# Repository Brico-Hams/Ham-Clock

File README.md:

# CYD Ham Dashboard – BricoHams edition

> **BricoHams edition** of the CYD Ham Dashboard, maintained by the BricoHams group with thanks to **EA5JEF, Diego** - **EA5KAO, Anatol**. It is based on the original project by [HenrysCat](https://github.com/HenrysCat/esp32-cyd-ham-dashboard) – many thanks for creating it. Documentation and the configuration manual are in [`docs/`](docs/README.md); full acknowledgements in [CREDITS.md](CREDITS.md).

A HamClock-inspired ham radio dashboard for the ESP32 Cheap Yellow Display, supporting both the 2.8" ESP32-2432S028R and the 4.0" 320x480 ST7796S variant from a single source tree.

**[Flash it in your browser with the Web Flasher](https://brico-hams.github.io/Ham-Clock/)**

## Reloj o Morse Tutor Bricohams

El suscriptor puede elegir entre **dos firmwares independientes**: este reloj,
o [Bricohams Morse Tutor](morse-tutor/README.md). Grabar uno sustituye al otro;
no se ha incorporado el tutor al bucle ni a las dependencias del reloj.
El [instalador del tutor](https://brico-hams.github.io/Ham-Clock/morse-tutor/)
se publica junto al existente mediante el workflow de GitHub Pages.

El tutor v2.1.1 es una nueva implementación Bricohams con menús por tarjetas,
perfil Freenove 3,2" FNK0114L/ST7789 y sala de mensajes para múltiples
tutores por ESP-NOW. Cada pantalla ofrece WiFi `Bricohams-CW-XXXXXX`
(clave `BricohamsCW`) para enviar desde el móvil sin Internet.
No es una red mesh ni RF de radioaficionado; consultar
[funcionamiento, límites y autoría](morse-tutor/README.md).
Incluye español, inglés, alemán, francés e italiano, con idioma de interfaz
y vocabulario independientes; entrenador eco, Koch configurable, práctica
adaptativa, ocho memorias, estadísticas y pausas Wordsworth.
En modo llave recta, el pulsador táctil **Llave CW** permite manipular y enviar
en Red CW sin llave externa, manteniendo pulsado para cada marca y soltando
para los espacios. En Iambic A/B conserva DIT/DAH virtuales.
El perfil Freenove es del tutor: no se añade automáticamente al reloj.

El subproyecto incluye una interfaz cableada de llave/audio con Gerber y cajas
paramétricas imprimibles para reloj con batería y tutor con palas mecánicas.
Son **prototipos pendientes de validación física**, no hardware certificado.
Consulta [alimentación, conexiones y fabricación](morse-tutor/hardware/README.md)
y [las medidas de las cajas](morse-tutor/mechanical/README.md) antes de fabricar.
El [tutorial ilustrado y manual detallado](https://brico-hams.github.io/Ham-Clock/morse-tutor/docs/manual.html)
incluye todos los ajustes y capturas web con datos simulados, además de
ilustraciones TFT claramente identificadas.
El [catálogo de cajas](https://brico-hams.github.io/Ham-Clock/morse-tutor/docs/cajas.html)
ofrece 36 bases/tapas de nueve variantes, incluidas Sunton 3,2" N/R/C y otras
familias documentadas. Las nuevas cajas no añaden perfiles de firmware ni
certifican el ajuste de las envolventes provisionales.

Los perfiles del reloj y del tutor fijan `espressif32@6.13.0` (Arduino-ESP32
2.0.17). El reloj utiliza la API LEDC 2.x; una plataforma sin versión puede
seleccionar Arduino 3.x y romper la compilación del instalador. No se ha cambiado
la lógica del reloj para corregirlo.

It provides a touch-controlled landscape dashboard — 320x240 on the 2.8" board, 480x320 on the 4.0" — with UTC/local time, HamQSL propagation data, a greyline map, DX spots, Wi-Fi setup, and a local web settings page. The 4.0" board uses the extra room rather than simply scaling up: larger text on the data pages, and twelve DX/POTA spots in place of eight.

## Features

- ESP32-2432S028R / CYD ILI9341 display support
- XPT2046 touch navigation
- Thirteen dashboard pages, plus an optional ISS tracker and an optional Music page (MP3 from microSD):
  - Clock
  - HF Propagation from HamQSL
  - VHF Conditions from HamQSL
  - Greyline map with QTH marker, sun marker, terminator, sunrise/sunset, and day/night status
  - PSKReporter reception reports for your callsign, plotted on the same world map
  - ISS Tracker: current position and ground track on the same world map, plus upcoming passes (optional; hidden until a free N2YO API key is set)
  - DX spots from JSON and/or a persistent Telnet DX Cluster connection
  - POTA activator spots, with an optional distance filter from your locator
  - OpenWebRX status and live chat
  - DMR Last Heard from compatible hotspots
  - World Clock with UTC and ten city clocks
  - Nearest APRS weather station and recent weather data
  - Nearby APRS nodes and stations, ordered by distance from your locator
  - Live APRS map: range-ring view centred on your QTH with every station heard in the last hour (tap to zoom)
- Captive portal Wi-Fi setup with up to five remembered networks; it automatically joins a saved network in range and switches off the hotspot a few seconds after connection (it can be switched back on from the web settings page if you need it again)
- Local web settings page on the device IP
- Hold the BOOT button on the back of the board for 5 seconds to factory reset all settings
- Optional mDNS address: `http://cyd-ham.local/`
- NTP time sync
- Configurable callsign, locator, timezone, data URLs, refresh intervals, and brightness
- Optional automatic page change, cycling only the pages you tick at your chosen interval
- Optional night dimming, fading the backlight between a day and a night level across sunrise and sunset
- Settings stored in ESP32 non-volatile preferences
- No LVGL, SD card, or external filesystem required

## Hardware

Three tested targets, plus one untested Freenove target, all ESP32-WROOM based with an XPT2046 resistive touch controller:

| Board | Panel | PlatformIO env | Setup header |
| --- | --- | --- | --- |
| ESP32-2432S028R 2.8" | ILI9341 320x240 | `esp32-2432s028r` | `include/User_Setup.h` |
| ESP32-2432S028R 2.8" | ST7789 320x240 | `esp32-2432s028r-st7789` | `include/User_Setup_ST7789.h` |
| CYD 4.0" | ST7796S 480x320 | `esp32-4in-st7796` | `include/User_Setup_ST7796.h` |
| Freenove ESP32 Display 3.2" (FNK0103L) | ST7789 320x240 | `freenove-32-st7789` | `include/User_Setup_Freenove32.h` |

**Freenove FNK0103 (3.2" ST7789):** same 320x240 layouts as the 2.8" CYD. The
touch controller shares the display bus and has no interrupt line, so touches are
detected from the pressure reading; the backlight is on GPIO27 and the speaker
amplifier is enabled by GPIO4. The pin map comes from the BricoHams Morse Tutor's
Freenove profile; the dashboard has not yet been tested on this board. If colours
or orientation are wrong, use the Display settings (swap red/blue, flip, mirror).

TFT_eSPI binds its panel driver at compile time, so the board is chosen by the
environment you build, not at runtime. Each environment force-includes its own
setup header, which carries the pins, the panel size, and the `DISPLAY_W` /
`DISPLAY_H` values the page layouts are derived from. Everything board-specific
lives in those headers rather than in the source.

### 2.8" wiring (ESP32-2432S028R)

| Signal | GPIO |
| --- | ---: |
| TFT MISO | 12 |
| TFT MOSI | 13 |
| TFT SCLK | 14 |
| TFT CS | 15 |
| TFT DC | 2 |
| TFT RST | -1 |
| TFT backlight | 21 |
| Touch SCLK | 25 |
| Touch MOSI | 32 |
| Touch MISO | 39 |
| Touch CS | 33 |
| Touch IRQ | 36 |

### 4.0" wiring (ST7796S)

The display pins match the 2.8" board. The two differences are the backlight,
which moves to GPIO 27, and the touch controller, which shares the display's
SPI bus instead of having its own. `dashboard_display.cpp` detects the shared
bus by comparing the touch pins against the TFT pins, and uses
`TFT_eSPI::getSPIinstance()` rather than starting a second bus.

| Signal | GPIO |
| --- | ---: |
| TFT MISO | 12 |
| TFT MOSI | 13 |
| TFT SCLK | 14 |
| TFT CS | 15 |
| TFT DC | 2 |
| TFT RST | -1 |
| TFT backlight | **27** |
| Touch SCLK | **14** (shared) |
| Touch MOSI | **13** (shared) |
| Touch MISO | **12** (shared) |
| Touch CS | 33 |
| Touch IRQ | 36 |

This board also sets `USE_HSPI_PORT`. GPIO 12/13/14/15 are the ESP32's native
HSPI pins, so the peripheral can drive them through IOMUX and run the panel at
80MHz; without it TFT_eSPI defaults to VSPI, routes the signals through the GPIO
matrix, and the display breaks up into coloured noise above about 27MHz.

Some CYD variants use different pins. If the display is blank, white, mirrored, or touch is wrong, check your board revision and adjust the setup header for your environment and the touch constants in `src/dashboard_display.cpp`.

### Setup hotspot and factory reset

On first boot (or whenever no Wi-Fi is configured), the device broadcasts a `CYD-HamClock-Setup` access point (password `hamclock`) so you can join it and open the captive portal to enter your Wi-Fi details. Once the device confirms it has joined your network, the hotspot automatically switches off. To bring it back later — for example to reach the settings page again without your router — check "Keep the setup hotspot switched on" in the Station section of the web settings page.

The board's BOOT button (GPIO0, on the back next to the USB connector) doubles as a factory reset button: hold it down for 5 seconds while the dashboard is running to wipe all saved settings (Wi-Fi credentials, callsign, locator, timezone, data sources, brightness) and reboot to defaults. The screen shows a countdown while the button is held; release early to cancel.

## Flashing A Release Binary

If a `.bin` firmware file is attached to a GitHub release, you can flash it without building from source. The panel driver is compiled in, so each board has its own binary — check the release notes and pick the one matching your display, as the wrong binary will boot but show nothing usable.

Install `esptool`:

```sh
python -m pip install esptool
```

Put the board into normal USB flashing mode, then flash the release binary. Replace `COM5` and the filename as needed:

```sh
esptool.py --chip esp32 --port COM5 --baud 460800 write_flash -z 0x10000 firmware.bin
```

If the release includes bootloader and partition binaries, use the release instructions for those exact offsets. For PlatformIO-built firmware, the application binary normally goes at `0x10000`.

After flashing, the board will start its setup access point if Wi-Fi is not configured.

### Publishing the Web Flasher

The browser flasher lives in [`webflasher/`](webflasher/index.html) and uses [ESP Web Tools](https://esphome.github.io/esp-web-tools/). `tools/build_webflasher.py --build` builds every board variant and stages the bootloader, partition table, `boot_app0` and application image with a `manifest.json` per board in `webflasher/firmware/`. The script refuses to run while `include/app_config.local.h` exists, because that file would compile your Wi-Fi password and API keys into the public images.

The `Web Flasher` GitHub Actions workflow runs the script and deploys `webflasher/` to GitHub Pages whenever a `v*` tag is pushed, or when it is started by hand. Enable Pages with the source set to **GitHub Actions** in the repository settings first.

## Building From Source

Install:

- VS Code
- PlatformIO extension
- USB serial driver for your ESP32 board if required

Clone the repository and open it in VS Code.

Copy the example config to a git-ignored local override file:

```sh
copy include\app_config.example.h include\app_config.local.h
```

On macOS/Linux:

```sh
cp include/app_config.example.h include/app_config.local.h
```

Set per-device Wi-Fi, locator, callsign, timezone, service URLs, and API keys in `include/app_config.local.h`. That file is ignored by Git. Alternatively, configure Wi-Fi and dashboard settings from the captive portal or local web page.

Build. With no environment given this builds **all three**, which is a useful
check that a change suits every board but is not what you want before a flash:

```sh
pio run
```

Build and upload one board. Always pass `-e`, or the upload runs for each
environment in turn and leaves the last one on the board:

```sh
pio run -e esp32-2432s028r      -t upload   # 2.8" ILI9341
pio run -e esp32-2432s028r-st7789 -t upload # 2.8" ST7789
pio run -e esp32-4in-st7796     -t upload   # 4.0" ST7796S
```

Open Serial Monitor:

```sh
pio device monitor
```

## First Boot And Wi-Fi Setup

The ESP32 starts a setup access point while also trying to connect to saved Wi-Fi credentials.

- AP name: `CYD-HamClock-Setup`
- AP password: `hamclock`
- Portal address: `http://192.168.4.1`

Join the setup AP from a phone or computer. The captive portal may open automatically. If it does not, browse to:

```text
http://192.168.4.1
```

The setup page lets you configure:

- Callsign
- Up to five Wi-Fi SSID/password pairs; existing saved networks remain available when adding another one
- Timezone preset, label, and POSIX timezone rule
- Maidenhead locator
- 12-hour or 24-hour local clock on the clock page
- Propagation data source
- DX source mode, JSON URL, and Telnet host/port
- Refresh intervals
- Automatic page change, with the dwell in seconds and which pages take part
- Backlight brightness, and optional night dimming with its own level and fade length
- Display colour swap/invert and orientation (90-degree rotate, 180-degree flip, mirror) for differently wired CYD panels
- Touch page navigation direction swap for differently wired touch controller variants

Settings are saved to ESP32 Preferences and persist after reboot.
Saved Wi-Fi passwords are never displayed. Leave a password field blank to keep it, use its checkbox to clear it for an open network, or clear its SSID to remove that remembered network.

## Local Web Settings

When connected to Wi-Fi, the same settings page is available on your LAN:

```text
http://device-ip/
```

The clock page shows the current IP address. If mDNS starts successfully, this address may also work:

```text
http://cyd-ham.local/
```

Available routes:

- `GET /` - settings and status page
- `POST /save` - save settings
- `GET /status` - JSON status
- `POST /reboot` - restart the ESP32

This web UI is intended for a trusted local network. It does not include authentication.

## Touch Controls

- Tap left side: next page
- Tap right side: previous page
- Tap centre on HF Propagation or VHF Conditions page: manual propagation refresh
- Tap centre on DX Spots page: manual DX refresh
- Tap centre on PSKReporter page: queue a manual PSKReporter refresh (it runs once the five minute minimum interval has elapsed)
- Tap centre on ISS Tracker page: manual position and pass refresh
- Tap centre on POTA Spots page: manual POTA refresh
- Music page: the button row above the footer plays/pauses, skips and sets the volume (see below)

The footer shows Wi-Fi status, NTP status, and current page number. On every page except the Clock it also shows the current UTC time (the Clock page omits this since it already shows a full UTC readout above).

The Automatic Page Change section of the web settings page can cycle the dashboard on its own. Set how many seconds each page is shown (3 to 600) and tick which pages take part; unticked pages are skipped by the cycle but are still reachable by tapping. The ISS Tracker page is the one exception: while it is switched off, or has no API key set, it is left out of both the cycle and the left/right tap navigation entirely, rather than just being unticked. Any tap restarts the countdown, so a page being read is not pulled away mid-look.

If a DX or POTA row is part way through scrolling in when the countdown expires, the change waits for the list to settle rather than cutting the slide off, then turns the page immediately. A three second grace cap keeps a busy Telnet feed from parking the rotation on one page.

## Night Dimming

The Display section of the web settings page can fade the backlight down after dark. Set a night brightness percent and a fade length in minutes, and the backlight moves between the daytime brightness and the night level across a window centred on each crossing: a 40 minute fade starts 20 minutes before sunset and finishes 20 minutes after, then reverses at sunrise.

Sunrise and sunset come from your Maidenhead locator, the same figures the Greyline page shows, so set the locator correctly first. The settings page prints the current sun state and today's sunrise and sunset next to the controls. Before NTP has synced, or with dimming switched off, the daytime brightness is used.

The `/status` endpoint reports `backlight` (the level actually being driven, which sits between the two settings during a fade) and `sun`, so the fade can be watched at dusk without staring at the panel.

## Dashboard Pages

### Clock

Shows:

- Large UTC time
- Configured local time, in 24-hour or 12-hour with AM/PM (web settings page, Time and Location)
- Date
- Callsign and Maidenhead locator
- Device IP
- Uptime
- Wi-Fi/NTP/footer status

### HF Propagation

Fetches HamQSL data directly by default:

```text
https://www.hamqsl.com/solarxml.php
```

Displays:

- SFI
- A index
- K index
- X-Ray
- Sunspots
- Solar wind speed (SW) and magnetic-field Bz
- Geomag
- Noise
- Aurora
- HamQSL band condition groups for day/night
- Last update time and status

An optional JSON proxy URL can be configured from the web page.

### VHF Conditions

Same layout and data source as HF Propagation, sharing the same refresh cycle and JSON proxy setting.

Displays:

- SFI, A index, K index, X-Ray, Sunspots, Solar wind/Bz, Geomag, Noise, Aurora (identical top rows to HF Propagation)
- HamQSL VHF phenomena: VHF Aurora (with auroral latitude, when supplied), and E-Skip conditions for 6m Europe, 4m Europe, 2m Europe, and 2m North America
- Last update time and status

### Greyline

Calculates locally using the configured Maidenhead locator and NTP time.

Displays:

- Bitmap-style world map
- QTH marker
- Sun/subsolar marker
- Day/night terminator
- Night-side shading
- Sunrise, sunset, UTC time
- Location/daylight/greyline status

Changing the Maidenhead locator refreshes the Greyline calculations and map immediately; no reboot is required.

### PSKReporter

Plots recent PSKReporter reception reports for the configured callsign on the same world map the Greyline page uses.

Displays:

- One marker per four-character grid square, coloured by band
- QTH marker
- Grid and report counts for the selected time window
- Furthest report (callsign, locator, great-circle distance)
- A legend naming only the bands currently present, each in its marker colour

Settings:

- `Direction`: `Who is hearing me` (default) queries `senderCallsign`; `Who I am hearing` queries `receiverCallsign`
- `Report window minutes`: how far back to ask for, 5 to 360, default 60
- `PSKReporter refresh minutes`: 5 to 120, default 5
- `Contact email`: optional, sent as `appcontact`

The page needs a callsign to work. With the callsign field blank it shows the map and a prompt to set one, and makes no requests.

### APRS Weather and Nearby Stations

Both pages use a receive-only TCP connection to APRS-IS with the standard
`pass -1` login and a server-side radius filter centered on the configured
Maidenhead locator. The Station callsign is used to identify the client; the
dashboard never transmits or gates packets. The connection starts the first
time an APRS page is opened and remains active in the background while Wi-Fi is
connected, so weather beacons can arrive between carousel visits.

`APRS nearby radius` in web settings accepts 10 to 300 km (default 100 km).
The weather page selects the closest weather-bearing position packet and shows
available APRS weather fields in metric units. The nearby page lists up to six
stations, sorted by distance; comments containing common digipeater, LoRa, DMR,
or repeater identifiers are labelled as nodes. Data availability depends on
stations transmitting within range and APRS-IS connectivity.

An optional personal APRS.fi API key can enrich the nearest station's weather
data. The key is requested only while the weather page is active, no more than
once every 15 minutes, and is never bundled as a shared key. APRS.fi is credited
on the weather page and in the settings page, with a link to its service. Before
distributing builds with this integration, each user must configure their own
key and the publisher should contact APRS.fi as required by its API terms.

PSKReporter asks that reception data is retrieved no more often than once every five minutes. The firmware enforces that as a hard floor: the refresh setting will not go below five minutes, and a manual refresh from the touch screen or from saving settings is queued rather than run immediately if the last request was more recent than that. A `503` response, which is how PSKReporter turns away a client querying too often, is shown as `Rate limited` on the status line.

Reports are read straight off the socket one XML element at a time and never buffered whole, so an active callsign returning hundreds of reports costs no more RAM than a quiet one. Up to 48 grid squares are plotted; the furthest-report line considers every report returned, not just the plotted ones.

### ISS Tracker

Plots the current position of the ISS on the same world map the Greyline and PSKReporter pages use, draws its ground track either side of now, and lists upcoming passes over your configured locator. Position and track are computed on-device with [SGP4](https://github.com/Hopperpop/Sgp4-Library) orbital propagation from a TLE fetched periodically from [Celestrak](https://celestrak.org/), so they update often (every 20 seconds) and cost no network requests beyond the daily TLE refresh. Passes still come from the free [N2YO](https://www.n2yo.com/api/) REST API's `radiopasses` endpoint, since correctly searching a topocentric elevation curve for AOS/max-elevation/LOS is exactly the kind of thing better left to a service that already does it, and N2YO's free-tier limit for that endpoint (100 requests/hour) comfortably covers an hourly refresh. `radiopasses` rather than `visualpasses` deliberately: hams care about any pass above the elevation threshold for an RF contact (APRS, voice repeater, SSTV), not just the rarer passes where the ISS is sunlit against a dark sky.

Displays:

- ISS marker on the world map, alongside the QTH marker
- Ground track for roughly the 45 minutes either side of now (about half the ISS's ~93 minute orbit), as a thin line; a segment is skipped rather than drawn wherever the track crosses the antimeridian
- Current latitude/longitude and altitude, in both km and miles
- Current azimuth and elevation - i.e. where to actually point - alongside the next pass line
- Next pass: rise time (UTC), maximum elevation, duration
- Every pass after that which still fits the row: four on the 2.8" boards, up to five on the 4.0" (matching the DX/POTA pages' precedent of the taller board showing more rows rather than just bigger text)

Settings:

- `Show ISS tracker page`: off by default
- `N2YO API key`: free, from [n2yo.com/api](https://www.n2yo.com/api/) — used only for the pass list; position and track work without it once the TLE has been fetched, but the page stays hidden until a key is set regardless

This is the one dashboard page that is not always present. With the checkbox off, or the key blank, it is left out of both the automatic page cycle and manual left/right navigation entirely — the dashboard behaves exactly as it did before this page existed. Turning it on and setting a key adds it immediately, no reboot required.

Passes are only searched up to two days out and down to a 10 degree minimum elevation, which is the same trade every ham pass predictor makes between screen space and usefulness.

### DX Spots

Supports three source modes:

- `Auto` (default): backfill the list from JSON, then keep a Telnet connection open and add live spots on top of it
- `JSON`: use only the configured JSON feed
- `Telnet`: maintain a connection to the configured DX Cluster

In `Auto`, JSON fills the list in one request so the page is useful within seconds of boot, and Telnet then delivers spots live, one at a time. Once Telnet is delivering it keeps the list and JSON is left alone; JSON refreshes again only while Telnet has yet to deliver, or if the connection drops or falls silent for 10 minutes. A Telnet connection that cannot reach the cluster does not disturb the JSON list on screen.

The default JSON endpoint is:

```text
https://web.cluster.iz3mez.it/spots.json
```

Displays recent spots with:

- Frequency
- Callsign
- Mode, inferred where possible
- UTC time
- Last update time and status

The list holds eight spots on the 2.8" boards and twelve on the 4.0". A new
Telnet spot pushes the rows down one pitch, animated by rendering the incoming
row and the rows already on screen into a sprite and pushing a shifted window of
it each frame.

The default Telnet cluster is `dxspots.com:7300`. The configured station callsign is used for login, or `NOCALL` if no callsign is set. Both sources are configurable from the web settings page.

The device keeps the last good spot list when a refresh or connection fails. The DX page shows whether the active data came from JSON, Telnet, or the last good result.

## Configuration Files

### `include/app_config.local.h`

Optional per-device defaults. Copy from `include/app_config.example.h`; this
file is ignored by Git so credentials and private service URLs stay local.

Useful defaults:

```cpp
#define WIFI_SSID ""
#define WIFI_PASSWORD ""
#define MAIDENHEAD_LOCATOR "AA00"
#define APP_SETTINGS_NAMESPACE "cyd-hamclock"
#define TIMEZONE_DEFAULT "UTC0"
#define TIMEZONE_LABEL_DEFAULT "UTC"
#define CALLSIGN_DEFAULT ""
#define OPENWEBRX_URL_DEFAULT ""
#define DMR_HOTSPOT_URL_DEFAULT ""
#define N2YO_API_KEY_DEFAULT ""
#define PROPAGATION_JSON_URL ""
#define DX_SPOTS_URL ""
```

`include/app_config.h` supplies safe generic fallbacks. Values saved through the captive portal or web settings page override most defaults at runtime.
When no DX URL has been saved, `DX_SPOTS_URL` is used if configured; otherwise the public IZ3MEZ endpoint is used.

### `include/User_Setup*.h`

TFT_eSPI display configuration. There is one per board, and PlatformIO
force-includes the right one from that environment's `build_flags`:

```ini
build_flags =
  -D USER_SETUP_LOADED=1
  -include include/User_Setup.h          ; or _ST7789.h / _ST7796.h
```

Because the header is force-included into every translation unit, the
`DISPLAY_W` and `DISPLAY_H` it defines are visible project-wide. The page
layouts derive their geometry from those two values, and `src/dx_spots.h` and
`src/pota_spots.h` use `DISPLAY_H` to size the spot arrays — eight rows on the
2.8" boards, twelve on the 4.0".

## Timezones

The web settings page includes common timezone presets. The firmware uses POSIX timezone strings.

UK default:

```text
GMT0BST-1,M3.5.0/1,M10.5.0/2
```

UTC:

```text
UTC0
```

If your country is not listed, choose `Custom POSIX TZ` and enter a POSIX rule manually.

### POTA Spots

Live Parks on the Air activator spots from `https://api.pota.app/spot/activator`.

Displays `Freq | Call | Mode | Park`, newest spot first. The park reference takes the column DX Spots uses for time, since the reference is what you need in order to log the contact.

New spots scroll in one at a time using the same animation as the DX Spots page. Both pages share one set of row state and one scroll sprite, since only one of them can be on screen at a time; they differ only in the header of the last column.

Settings:

- `Max distance km`: great-circle distance from your Maidenhead locator. `0` (the default) shows everything.
- `POTA refresh minutes`: 1 to 120, default 5.
- `Hide RBN spots`: RBN entries are posted automatically by skimmers rather than by a person.

The status line reports how many spots were shown out of how many the feed returned, plus how many the filters rejected, so a short list explains itself.

Notes and limits:

- POTA publishes no formal rate limit. Existing client libraries settle on one request a minute, so that is enforced as a hard floor regardless of the refresh setting.
- The feed returns roughly a hundred spots in no guaranteed order. They are read one JSON object at a time and never buffered as a whole array, and the newest eight that pass the filters are kept.
- Repeat spots of the same activator at the same park are collapsed into one row, so a heavily spotted station cannot crowd out everyone else.
- Spots without coordinates are always shown, even when a distance limit is set, since there is no way to tell whether they are near or far.
- SOTA is deliberately not included. The `api2.sota.org.uk` endpoint currently returns a notice that it is deprecated and due for removal, so it is left until the replacement API is settled.

## Data Refresh

Default refresh intervals:

- HF Propagation: 15 minutes
- DX JSON: 5 minutes
- DX Telnet: persistent connection with reconnect attempts limited to once every 30 seconds
- PSKReporter: 5 minutes, which is also the lowest interval the service permits
- POTA: 5 minutes, with a one minute hard floor
- ISS Tracker: position/track every 20 seconds (local SGP4 computation, no network cost), TLE once a day, passes every hour (all fixed, not user-configurable)
- Greyline calculations: once per minute
- Clock: once per second

Propagation, DX, and PSKReporter refresh intervals can be changed in the web settings page.

## Project Structure

```text
include/
  User_Setup.h              TFT_eSPI pin setup, 2.8" ILI9341
  User_Setup_ST7789.h       TFT_eSPI pin setup, 2.8" ST7789
  User_Setup_ST7796.h       TFT_eSPI pin setup, 4.0" ST7796S
  app_config.example.h      Example local config
  greyline_map.h            Embedded Greyline map bitmap, 300x150
  greyline_map_460x230.h    Embedded Greyline map bitmap, 4.0" board

src/
  main.cpp              App entry point
  connectivity.*        Wi-Fi, NTP, timezone handling
  settings.*            Preferences-backed settings
  setup_portal.*        Captive portal and LAN web settings
  dashboard_display.*   TFT UI, touch, page rendering
  propagation.*         HamQSL fetch and parsing
  greyline.*            Solar and greyline calculations
  psk_reporter.*        PSKReporter query, streaming XML parse, rate limiting
  pota_spots.*          POTA spot fetch, streaming JSON parse, distance filter
  dx_spots.*            DX JSON fetch plus Telnet connection and parsing
  iss_tracker.*         SGP4 position/track from a fetched TLE, plus N2YO pass fetch
```

## Music Player (microSD)

An optional last page, **Music**, plays MP3 files from a microSD card through the
board's speaker: copy them into `/Music` on a FAT32 card, insert it before power-up
and connect a small speaker. The page stays hidden without a card or MP3 files,
and is never picked by the automatic page change. Controls: previous, play/pause,
next, volume down/up. On the CYD boards audio is 1-bit PDM on GPIO26 (modest
quality); the Freenove board uses the ESP32's DAC. Adding the SD card means the
2.8" CYD now bit-bangs its touch controller. Built for all four boards but not yet
tested on hardware. Details: [docs/modules/music.md](docs/modules/music.md).

The idea comes from Freenove's
[LVGL Music tutorial](https://docs.freenove.com/projects/fnk0103/en/latest/fnk0103/codes/tutorial/17_LVGL_Music.html);
Freenove's code (CC BY-NC-SA 3.0) is not used.

## Notes And Limits

- The setup AP remains available while the device runs.
- The web UI is for trusted LAN use only.
- Telnet reading is non-blocking; connection attempts use a short bounded timeout.
- SD card storage is not required; it is only used by the optional Music page.
- LVGL is not used.
- The embedded Greyline map uses flash space; current firmware size is close to the default app partition limit. All three environments use `min_spiffs.csv` to get a large enough app partition. The 4.0" build is the biggest, as it carries a 460x230 map instead of 300x150.
- The Greyline and PSKReporter maps are composed and pushed one horizontal band at a time rather than as a single sprite, so the map visibly draws in stages. That is deliberate: the 4.0" map would need a 211,600-byte contiguous allocation against a largest free block of about 110,000, so it could not be drawn any other way. Band height is set per board by `MAP_BAND_ROWS` and must divide the map height exactly.

## Troubleshooting

### Display is blank or white

Check that your CYD uses the same display pins as the setup header for the
environment you built, and that you flashed the environment matching your panel.

### Display shows random coloured pixels

The panel is receiving SPI it cannot follow. Before reaching for a lower
`SPI_FREQUENCY`, check which SPI port the build is using. On a board wired to
GPIO 12/13/14/15 — the ESP32's native HSPI pins — TFT_eSPI's default VSPI has to
route those signals through the GPIO matrix, and the added delay makes anything
near 40MHz unreliable. Setting `USE_HSPI_PORT` in the setup header moves them
onto IOMUX and the same panel runs at 80MHz.

This is worth checking first because lowering the clock hides the fault at a
real cost: it is roughly a third of the draw rate, which shows up as a visibly
slow spot-list scroll and a slow map redraw.

### Touch is inaccurate

The touch calibration constants are in `src/dashboard_display.cpp`. CYD touch panels vary slightly.

### Time does not sync

Check Wi-Fi status and confirm your network allows NTP. The footer shows `NTP OK` when synced.

### Web page does not open

Check the IP shown on the clock page and browse to:

```text
http://that-ip/
```

If `cyd-ham.local` does not resolve, use the IP address instead.

### Propagation or DX shows fetch failed

Confirm Wi-Fi is connected and that your network allows HTTPS requests to the configured data source.

## Credits

- Original CYD Ham Dashboard: **HenrysCat** – <https://github.com/HenrysCat/esp32-cyd-ham-dashboard>
- BricoHams edition: **BricoHams**, with thanks to **EA5JEF, Diego**
**BricoHams**, with thanks to **EA5KAO, Anatol**
- Libraries and data services: see [CREDITS.md](CREDITS.md)

Released under the GNU General Public License v3.0, like the original project.

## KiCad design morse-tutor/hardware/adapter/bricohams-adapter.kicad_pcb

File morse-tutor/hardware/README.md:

# Llave, audio y batería — Bricohams

## Alcance y límites

La primera referencia es la CYD ESP32-2432S028R de 2,8". Su pinout se ha
contrastado con [PINS.md de ESP32-Cheap-Yellow-Display](https://github.com/witnessmenow/ESP32-Cheap-Yellow-Display/blob/main/PINS.md).
Los pines TFT/táctil y la variante ST7796 proceden de los perfiles de Ham-Clock.
No se ha confirmado el conector de expansión de la CYD de 4": no trasladar
la numeración del conector de 2,8" a otra placa.

El nuevo perfil de firmware Freenove 3,2" FNK0114L **no convierte este
adaptador en un shield compatible**. En Freenove GPIO27 es backlight,
el táctil comparte HSPI y el audio usa DAC25/DAC26 con habilitación GPIO4.
Los contactos externos se mantienen deshabilitados hasta verificar el
conector real; no aplicar el arnés DIT22/DAH27 de esta documentación.
Consultar [el perfil y sus fuentes oficiales](../README.md#pantallas-y-wokwi).

**No conectar nada con la placa encendida.** Antes de alimentar, comprobar con
multímetro polaridad, continuidad y ausencia de cortocircuito entre 3,3 V/5 V/GND.
Las entradas del ESP32 son de **3,3 V**, no toleran 5 V.

## Llave recta o palas en CYD de 2,8"

| Función | GPIO / conexión |
|---|---|
| DIT | GPIO22, disponible en P3 y CN1 |
| DAH | GPIO27, disponible en CN1 |
| Común de llave | GND |
| Pull-ups externos del adaptador | 3,3 V de CN1 |
| Jack TRS de 3,5 mm | Punta = DIT, anillo = DAH, manguito = GND |
| Llave recta | Contacto seco entre DIT y GND; usar modo llave recta |

Comprobar **las etiquetas y orientación** del conector de cada unidad;
los cables comerciales pueden invertir colores. No se suministra un arnés
con orden de colores supuesto. Una llave mono TS puede poner DAH a masa:
usar un cable TRS o asegurar la configuración de llave recta.

Los contactos mecánicos y la llave externa están en paralelo. Se pueden usar
ambos conectores, pero no manipular dos llaves simultáneamente.
GPIO35 es otra entrada documentada, pero carece de pull-up interno; sólo usarlo
como alternativa configurada con pull-up externo. No es el valor predeterminado.

## Audio nativo y externo

- En la CYD habitual de 2,8", GPIO26 llega al amplificador de la placa y al
  conector de altavoz **P4**. P4 no es un GPIO ni una salida de línea.
  La carga e impedancia admisibles deben comprobarse en el esquema de la
  revisión comprada. Comenzar con carga/volumen apropiados al amplificador.
- Para altavoces activos, el adaptador toma **la señal de GPIO26 antes del
  amplificador**, no P4. Esto puede requerir soldar un cable: GPIO26 no figura
  como pin libre de los conectores GPIO. Si no se sabe identificarlo, no hacer
  esa modificación; utilizar la salida nativa.
- R5=10 kΩ y R6=1 kΩ atenúan aproximadamente 11:1 el PWM de 3,3 V.
  C3=1 µF no polar elimina la componente continua hacia la entrada de línea.
  El nivel final depende de la impedancia del equipo conectado.
- Para altavoz pasivo sin amplificador nativo utilizable, conectar J5 a
  **un módulo amplificador de audio ya montado**, con entrada de alta impedancia
  y alimentación de 5 V, por ejemplo PAM8403. Un altavoz pasivo **no** se conecta
  directamente a GPIO26 ni a J4/J5.
- El módulo amplificador no va integrado como chip en este PCB; debe montarse
  aislado y sujeto, con su propia documentación. Emplear sólo un canal, empezar
  a volumen mínimo y limitar el consumo del adaptador a 0,5 A.
  Si se necesita más potencia, alimentar el módulo directamente desde una
  fuente adecuada, no a través de estas pistas.
- En amplificadores BTL los dos terminales del altavoz son activos:
  **no conectar ninguno a GND** ni a la masa de una entrada de línea.

No se ha medido el ruido PWM ni la compatibilidad con cada revisión de amplificador.
La salida es un tono de práctica, no un códec, entrada de micrófono ni salida RF.

## Adaptador cableado, no shield

Archivos en [adapter/](adapter/):

- `bricohams-adapter.kicad_pcb`: placa editable de dos capas, 80 × 40 × 1,6 mm.
- `gerber/`: cobre superior/inferior, máscaras, serigrafía superior, contorno,
  taladro metalizado y taladro no metalizado.
- `bricohams-gerber-r1.zip`: el mismo juego de Gerber y taladros, empaquetado.
- `schematic.svg`: esquema de conectividad por etiquetas de red.
- `assembly.svg`: dibujo de montaje, **vista superior**.
- `BOM.csv`, `design.json`, `validation.json`: componentes, datos y comprobaciones.

Los conectores son **pads para soldar cables**, no footprints de jacks ni un
conector que se enchufe directamente a la CYD. Los jacks son de panel; verificar
sus contactos con multímetro. Los pads de J1 tienen paso de 5 mm; no montar
un header de 2,54 mm sobre ellos.

| Pad | Señal | Destino |
|---|---|---|
| J1.1 | GND | Masa de CYD |
| J1.2 | 3V3 | 3,3 V de CYD |
| J1.3 | GPIO_DIT | GPIO22 en el perfil habitual de 2,8" |
| J1.4 | GPIO_DAH | GPIO27 en el perfil habitual de 2,8" |
| J1.5 | AUDIO_PWM | GPIO26 antes del amplificador, si se accede de forma segura |
| J1.6 | 5V | 5 V regulados y protegidos, nunca la celda Li-ion |
| J2.1 / J2.2 / J2.3 | GND / KEY_DIT / KEY_DAH | Jack de llave externa |
| J3.1 / J3.2 / J3.3 | GND / KEY_DIT / KEY_DAH | Común y contactos de palas integradas |
| J4.1 / J4.2 | LINE_OUT / GND | Altavoz activo |
| J5.1 / J5.2 / J5.3 | 5V / GND / LINE_OUT | Alimentación y entrada de módulo amplificador |

R1/R2=1 kΩ están en serie con las entradas; R3/R4=10 kΩ son pull-ups a 3,3 V;
C1/C2=10 nF son filtros. No ofrecen aislamiento galvánico ni una clasificación
ESD garantizada. **No usar como interfaz de manipulación para un transceptor**:
una salida de radio puede tener tensiones incompatibles.

El generador comprueba continuidad de las diez redes y distancias geométricas
entre cobres de redes distintas. Los resultados no sustituyen ERC/DRC de KiCad,
revisión CAM del fabricante ni ensayos eléctricos. **R1 es un prototipo**:
antes de fabricar, abrirlo en KiCad, ejecutar DRC, revisar la vista Gerber y
encargar sólo una muestra. No declarar el PCB validado para producción.

## Batería para ambos equipos

La opción prevista es un **power bank USB comercial cerrado**, con protección
y salida regulada de 5 V, conectado al USB de la pantalla. La caja dispone de
hueco para una envolvente de hasta **100 × 60 × 22 mm** y paso de cable.
No se recomienda una marca ni se presupone que cualquier power bank cabe.

- No conectar una celda de 3,7 V al pin de 3,3 V ni al USB.
- No se ha diseñado un cargador de litio, BMS, cargador TP4056 ni circuito
  de reparto de carga. El PCB de llave/audio no carga baterías.
- Elegir un power bank que no se apague con la carga real de la pantalla.
  Medir el consumo con la retroiluminación y el audio previstos.
- La carga simultánea mientras se usa sólo es admisible si el fabricante
  declara soporte de *pass-through*. En caso contrario, apagar y retirar/
  desconectar el power bank para cargarlo según sus instrucciones.
- Para flashear, desconectar la alimentación de batería de la pantalla antes
  de conectar el USB del ordenador. No alimentar dos fuentes en paralelo ni
  unir sus salidas de 5 V sin un circuito de conmutación apropiado.
- Fijar el power bank sin presionar su envolvente, dejando espacio para cables
  y ventilación. No usar baterías hinchadas, dañadas o sin protección.
  No cargar el equipo encerrado ni dejarlo expuesto al sol o dentro de un coche.
- No hay medida de porcentaje de batería: la pantalla no tiene un sensor
  instalado para ello y el firmware no inventa un nivel de carga.

Autonomía orientativa, no medida:
`horas ≈ capacidad_Wh × eficiencia / (5 V × consumo_A)`.
Un pack etiquetado 3000 mAh a 3,7 V contiene unos 11,1 Wh; con eficiencia
0,8 y un consumo **supuesto** de 0,35 A, el cálculo da unas 5,1 horas.
Cambiar esos valores por medidas reales; mAh a 3,7 V no son mAh a 5 V.

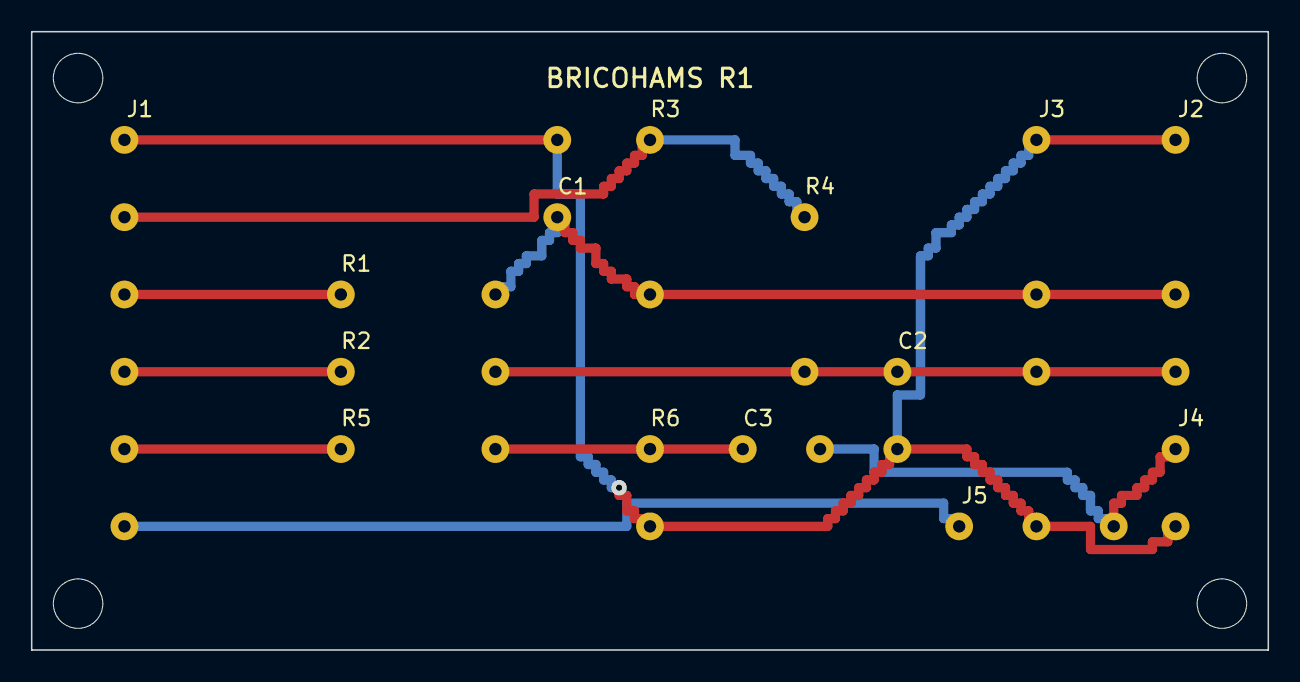
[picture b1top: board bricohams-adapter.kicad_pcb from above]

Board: 2 copper layers, 80.0 x 40.0 mm, 14 parts (0 on the bottom side), 10 nets.

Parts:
C1: 10nF, 5 mm; C1
C2: 10nF, 5 mm; C2
C3: 1uF nonpolar film, 5 mm; C3
J1: CYD wire pads, 5 mm pitch; J1
J2: External KEY: sleeve, tip, ring; J2
J3: Integrated paddle contacts: common, dit, dah; J3
J4: Active speaker: signal, ground; J4
J5: External amp: 5V, GND, IN; J5
R1: 1k, axial 10 mm; R1
R2: 1k, axial 10 mm; R2
R3: 10k, axial 10 mm; R3
R4: 10k, axial 10 mm; R4
R5: 10k, axial 10 mm; R5
R6: 1k, vertical axial 5 mm; R6

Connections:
3V3: J1.2, R3.1, R4.1
5V: J1.6, J5.1
ATTENUATED: C3.1, R5.2, R6.1
AUDIO_PWM: J1.5, R5.1
GND: C1.2, C2.2, J1.1, J2.1, J3.1, J4.2, J5.2, R6.2
GPIO_DAH: J1.4, R2.1
GPIO_DIT: J1.3, R1.1
KEY_DAH: C2.1, J2.3, J3.3, R2.2, R4.2
KEY_DIT: C1.1, J2.2, J3.2, R1.2, R3.2
LINE_OUT: C3.2, J4.1, J5.3

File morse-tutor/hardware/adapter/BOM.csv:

Reference,Value,Mounting
"J1","CYD wire pads, 5 mm pitch","THT/wired"
"J2","External KEY: sleeve, tip, ring","THT/wired"
"J3","Integrated paddle contacts: common, dit, dah","THT/wired"
"R1","1k, axial 10 mm","THT/wired"
"R2","1k, axial 10 mm","THT/wired"
"R3","10k, axial 10 mm","THT/wired"
"R4","10k, axial 10 mm","THT/wired"
"C1","10nF, 5 mm","THT/wired"
"C2","10nF, 5 mm","THT/wired"
"R5","10k, axial 10 mm","THT/wired"
"R6","1k, vertical axial 5 mm","THT/wired"
"C3","1uF nonpolar film, 5 mm","THT/wired"
"J4","Active speaker: signal, ground","THT/wired"
"J5","External amp: 5V, GND, IN","THT/wired"
